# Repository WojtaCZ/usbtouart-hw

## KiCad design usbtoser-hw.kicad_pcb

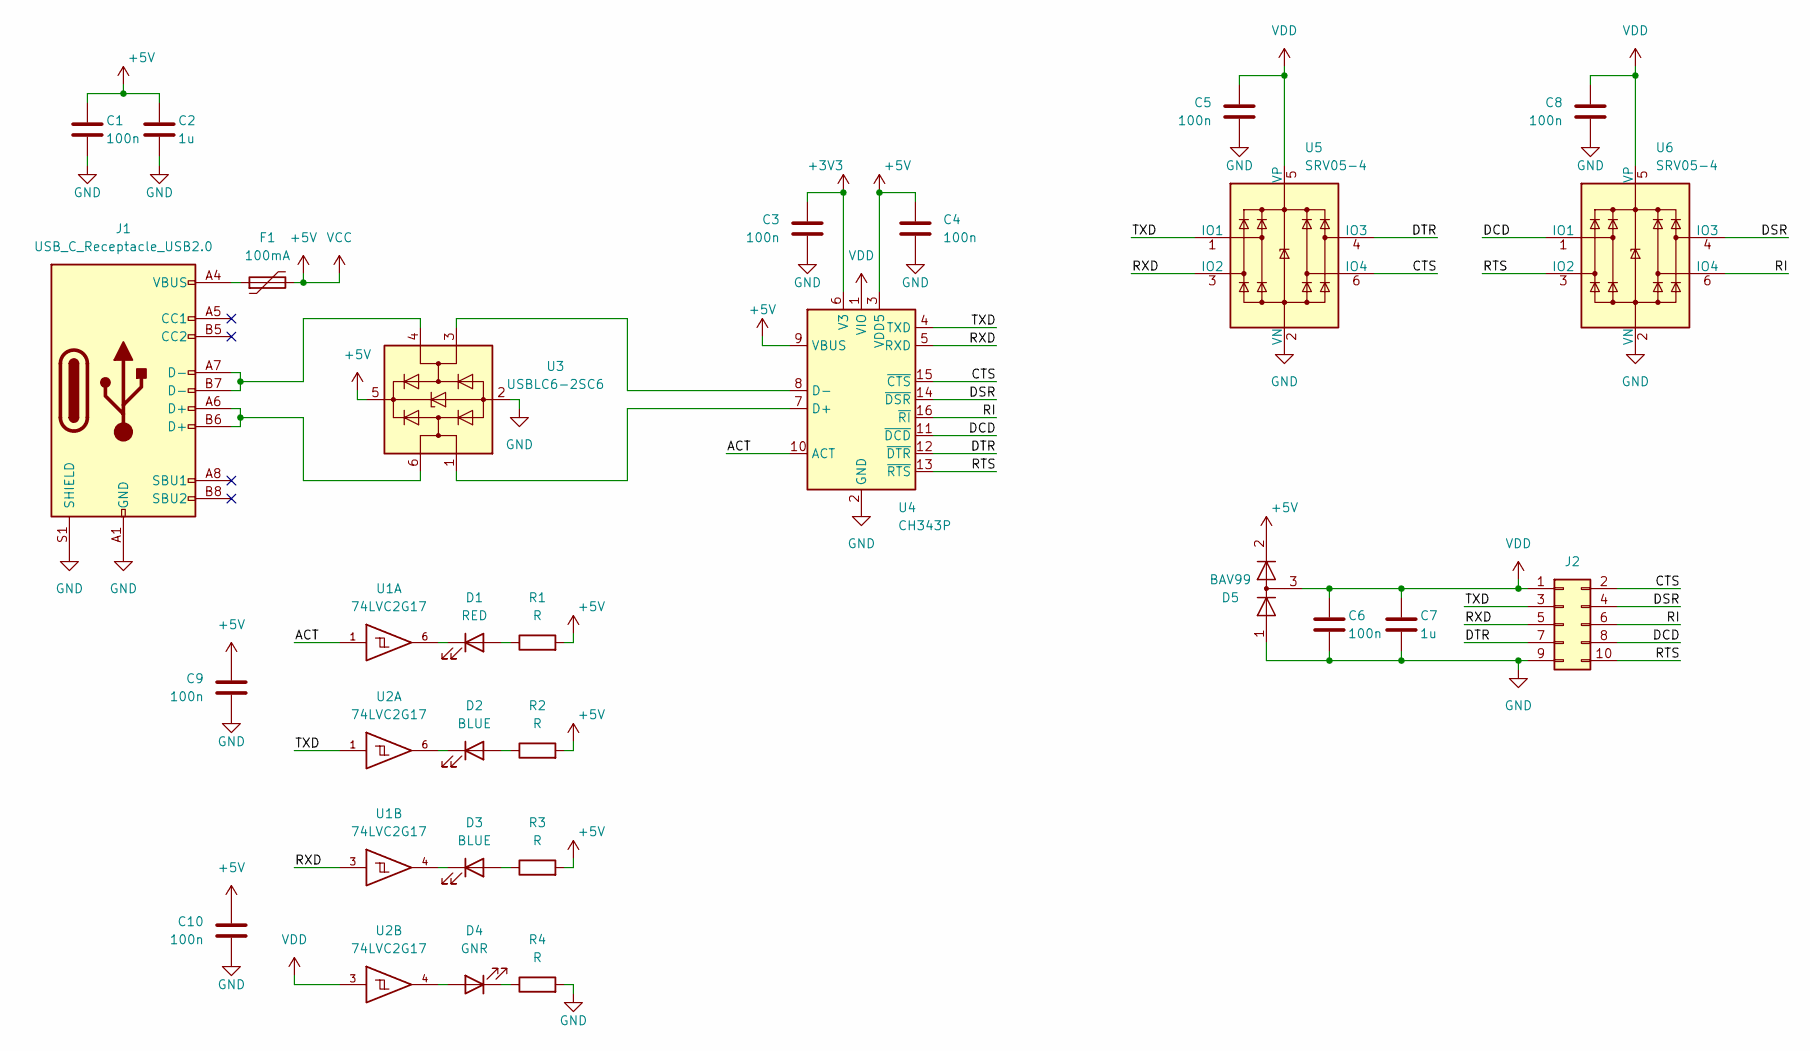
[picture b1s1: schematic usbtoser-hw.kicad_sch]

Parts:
C1, C3, C4, C5, C6, C8, C9, C10: 100n; C_0603_1608Metric
C2, C7: 1u; C_0603_1608Metric
D1: RED; LED_0603_1608Metric
D2, D3: BLUE; LED_0603_1608Metric
D4: GNR; LED_0603_1608Metric
D5: BAV99; SOT-23
F1: 100mA; Fuse_0603_1608Metric
J1: USB_C_Receptacle_USB2.0; USB_C_Receptacle_XKB_U262-16XN-4BVC11
J2: Conn_02x05_Odd_Even; IDC-Header_2x05_P2.54mm_Vertical
R1, R2, R3, R4: R; R_0603_1608Metric
U1, U2: 74LVC2G17; TSOP-6_1.65x3.05mm_P0.95mm
U3: USBLC6-2SC6; SOT-23-6
U4: CH343P; QFN-16-1EP_3x3mm_P0.5mm_EP1.7x1.7mm_ThermalVias
U5, U6: SRV05-4; SOT-23-6

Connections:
+3V3: C3.1, U4.6 (V3)
+5V: C1.1, C2.1, C4.1, C9.1, C10.1, D5.2 (A), F1.2, R1.2, R2.2, R3.2, U1.5 (VCC), U2.5 (VCC), U3.5 (VBUS), U4.3 (VDD5), U4.9 (VBUS)
/ACT: U1.1, U4.10 (ACT)
/CTS: J2.2, U4.15 (~CTS), U5.6 (IO4)
/DCD: J2.8, U4.11 (~DCD), U6.1 (IO1)
/DSR: J2.4, U4.14 (~DSR), U6.4 (IO3)
/DTR: J2.7, U4.12 (~DTR), U5.4 (IO3)
/RI: J2.6, U4.16 (~RI), U6.6 (IO4)
/RTS: J2.10, U4.13 (~RTS), U6.3 (IO2)
/RXD: J2.5, U1.3, U4.5 (RXD), U5.3 (IO2)
/TXD: J2.3, U2.1, U4.4 (TXD), U5.1 (IO1)
GND: C1.2, C2.2, C3.2, C4.2, C5.2, C6.2, C7.2, C8.2, C9.2, C10.2, D5.1 (K), J1.A1 (GND), J1.A12 (GND), J1.B1 (GND), J1.B12 (GND), J1.S1 (SHIELD), J2.9, R4.2, U1.2 (GND), U2.2 (GND), U3.2 (GND), U4.2 (GND), U4.17 (GND), U5.2 (VN), U6.2 (VN)
unnamed: D1.1 (K), U1.6
unnamed: D1.2 (A), R1.1
unnamed: D2.1 (K), U2.6
unnamed: D2.2 (A), R2.1
unnamed: D3.1 (K), U1.4
unnamed: D3.2 (A), R3.1
unnamed: D4.1 (K), R4.1
unnamed: D4.2 (A), U2.4
unnamed: F1.1, J1.A4 (VBUS), J1.A9 (VBUS), J1.B4 (VBUS), J1.B9 (VBUS)
unnamed: J1.A6 (D+), J1.B6 (D+), U3.6 (I/O1)
unnamed: J1.A7 (D-), J1.B7 (D-), U3.4 (I/O2)
unnamed: U3.1 (I/O1), U4.7 (D+)
unnamed: U3.3 (I/O2), U4.8 (D-)
VDD: C5.1, C6.1, C7.1, C8.1, D5.3 (K), J2.1, U2.3, U4.1 (VIO), U5.5 (VP), U6.5 (VP)

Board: 2 copper layers, 28 parts (0 on the bottom side), 26 nets, no tracks yet.
